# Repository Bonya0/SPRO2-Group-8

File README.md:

# SPRO2-Group-8

This is the github repository for the Electronics Semester Project Group 8.

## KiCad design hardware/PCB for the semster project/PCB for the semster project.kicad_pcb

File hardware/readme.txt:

This is the folder for hardware related files.

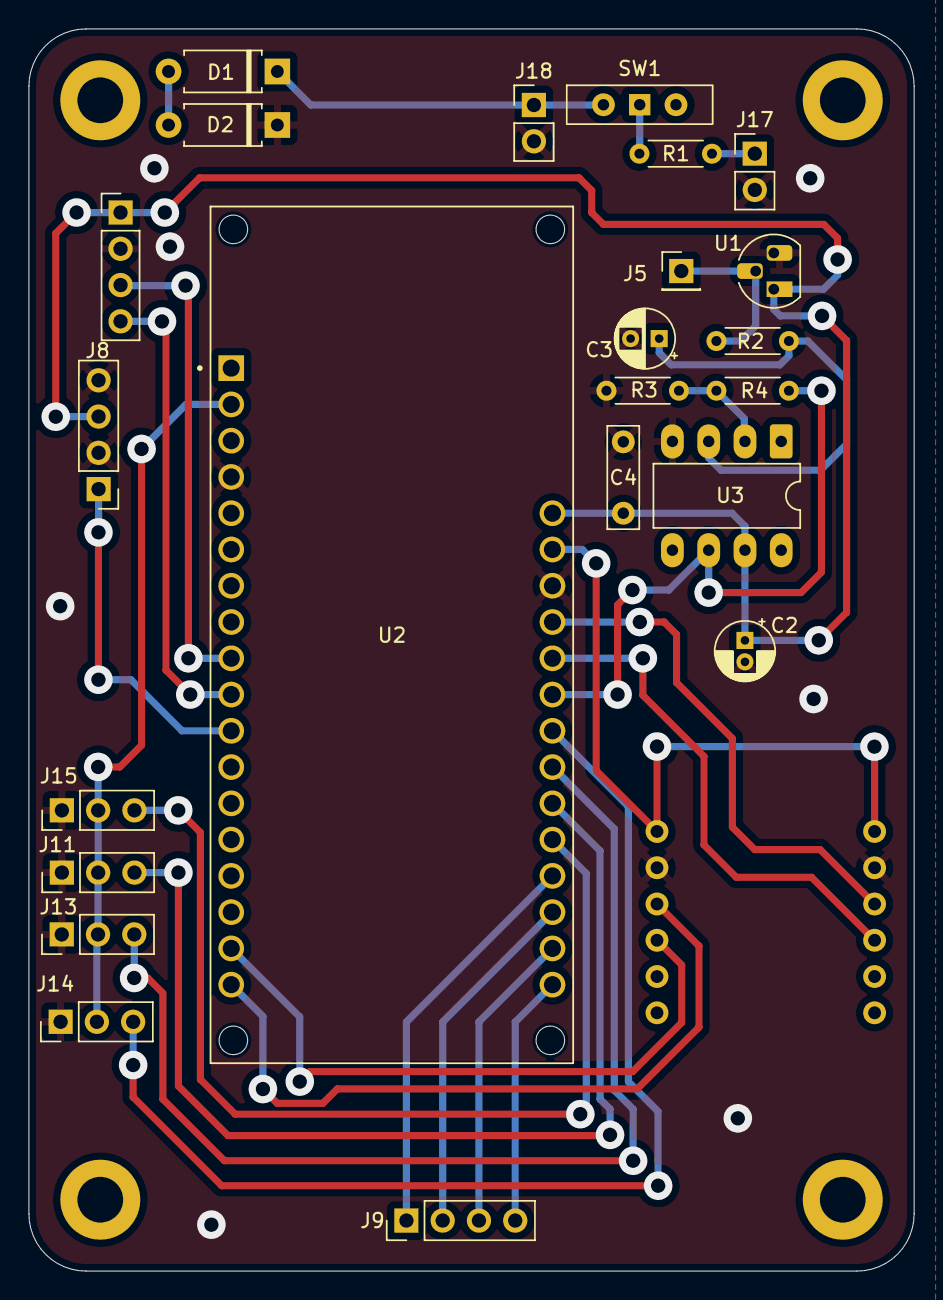
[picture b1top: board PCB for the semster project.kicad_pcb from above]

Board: 2 copper layers, 62.0 x 87.0 mm, 24 parts (1 on the bottom side), 24 nets.

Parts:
C2: 1uF; CP_Radial_D4.0mm_P1.50mm
C3: 150uF; CP_Radial_D4.0mm_P2.00mm
C4: 10nF; C_Rect_L7.0mm_W2.0mm_P5.00mm
D1, D2: D_Zener_Filled; D_A-405_P7.62mm_Horizontal
J1, J8, J9: LED conectors; PinHeader_1x04_P2.54mm_Vertical
J5: Conn_01x01_Pin; PinHeader_1x01_P2.54mm_Vertical
J11, J13, J14, J15: Conn_01x03_Pin; PinHeader_1x03_P2.54mm_Vertical
J17, J18: Conn_01x02_Pin; PinHeader_1x02_P2.54mm_Vertical
M1: SEN0344
R1: 120; R_Axial_DIN0204_L3.6mm_D1.6mm_P5.08mm_Horizontal
R2, R3, R4: 1k; R_Axial_DIN0204_L3.6mm_D1.6mm_P5.08mm_Horizontal
SW1: SW_Wuerth_450301014042; SW_Slide-03_Wuerth-WS-SLTV_10x2.5x6.4_P2.54mm
U1: LM35-LP; TO-92L_HandSolder
U2: DFR0654; MODULE_DFR0654
U3: CA3140; DIP-8_W7.62mm_LongPads

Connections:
/+3.3V: J1.1, J8.3, J11.2, J13.2, J14.2, J15.2, M1.1 (3V3), M1.12 (3V3), U1.1 (+V_{S}), U2.2 (3.3V), U2.31 (3.3V)
GND: C2.2, C3.2, C4.2, D2.1 (K), J1.2, J8.2, J8.4, J11.1, J13.1, J14.1, J15.1, J17.2, J18.2, M1.2 (GND), M1.11 (GND), R3.2, U1.3 (GND), U2.4 (GND), U2.30 (GND), U3.4 (V-)
unnamed: D1.2 (A), D2.2 (A)
unnamed: D1.1 (K), J18.1, SW1.2 (C)
unnamed: C2.1, C4.1, U2.32 (VCC), U3.7 (V+)
unnamed: J9.1, U2.22 (D13)
unnamed: J9.2, U2.21 (D12)
unnamed: J9.3, U2.20 (D11)
unnamed: J9.4, U2.19 (D10)
unnamed: J11.3, U2.24 (A1)
unnamed: J13.3, U2.25 (A2)
unnamed: J14.3, U2.26 (A3)
unnamed: J15.3, U2.23 (A0)
unnamed: J17.1, R1.1
unnamed: M1.10 (RX), U2.18 (RX)
unnamed: M1.9 (TX), U2.17 (TX)
unnamed: R1.2, SW1.1 (B)
unnamed: R4.2, U3.6
unnamed: C3.1, R2.1, U3.3 (+)
unnamed: R3.1, R4.1, U3.2 (-)
SCL: J1.3, M1.3 (SCL), U2.9 (SCL), U2.29 (SCL)
SDA: J1.4, M1.4 (SDA), U2.10 (SDA), U2.28 (SDA)
SIG: J8.1, U2.11 (D9)
VOUT: J5.1, U1.2 (V_{OUT}), U2.27 (A4)

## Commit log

2025-03-24 Kicad file
2025-03-24 Add files via upload
    This files contains 2 main subfolders: Namely the DFROBOTS SEN0344 schematic and footprints in the folder labelled MAX and, the DFROBOTS Esp32 devkit
2025-03-26 organizing
2025-03-26 organize
2025-04-30 code-1
2025-04-30 code-2
2025-05-05 code3
2025-05-29 final-touches
2025-06-02 final-code
